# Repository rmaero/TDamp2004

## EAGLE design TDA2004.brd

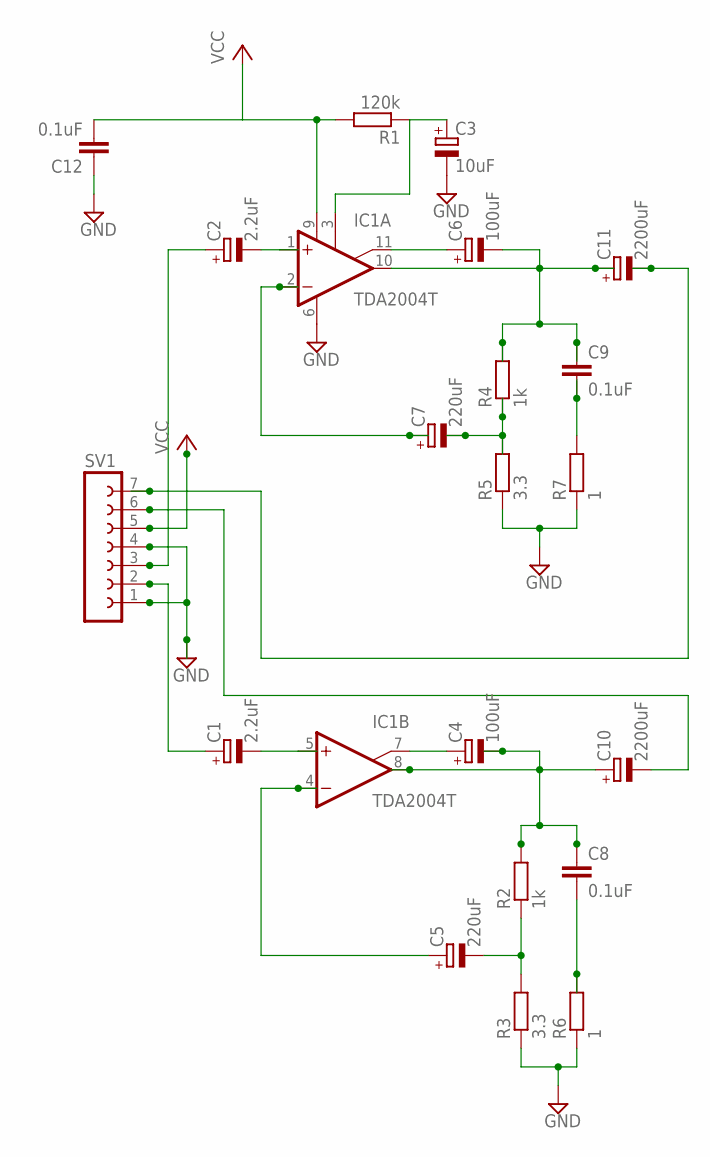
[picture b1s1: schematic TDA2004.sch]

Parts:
C1, C2: 2.2uF; B45181B
C3: 10uF; B45181B
C4, C6: 100uF; E2,5-5
C5, C7: 220uF; B45181B
C8, C9, C12: 0.1uF; C025-024X044
C10, C11: 2200uF; E5-10,5
IC1: TDA2004T; SIP11
R1: 120k; 0207/10
R2, R4: 1k; 0207/10
R3, R5: 3.3; 0207/10
R6, R7: 1; 0207/10
SV1: FE07-1; FE07

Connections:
GND: C3.-, C12.1, IC1.6 (GND), R3.1, R5.1, R6.1, R7.1, SV1.1, SV1.4
unnamed: C3.+, IC1.3 (SVRR), R1.1
unnamed: C9.2, R7.2
unnamed: C6.-, C9.1, C11.+, IC1.10 (OUT), R4.2
unnamed: C6.+, IC1.11 (BTSP)
unnamed: C2.-, IC1.1 (+IN)
unnamed: C7.+, IC1.2 (-IN)
unnamed: C10.-, SV1.6
unnamed: C4.+, IC1.7 (BTSP)
unnamed: C7.-, R4.1, R5.2
unnamed: C1.-, IC1.5 (+IN)
unnamed: C5.-, R2.1, R3.2
unnamed: C8.2, R6.2
unnamed: C11.-, SV1.7
unnamed: C5.+, IC1.4 (-IN)
unnamed: C4.-, C8.1, C10.+, IC1.8 (OUT), R2.2
unnamed: C1.+, SV1.2
unnamed: C2.+, SV1.3
VCC: C12.2, IC1.9 (V+), R1.2, SV1.5

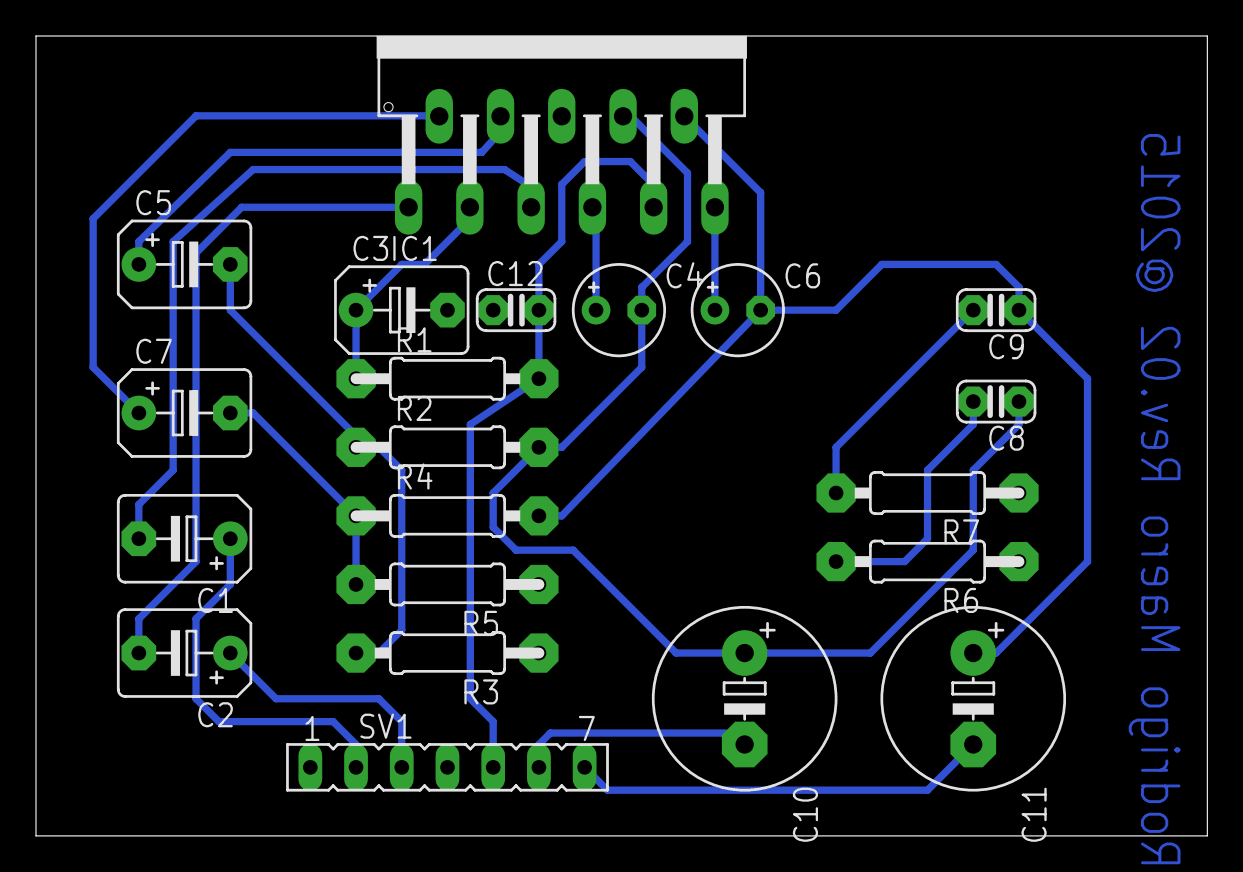
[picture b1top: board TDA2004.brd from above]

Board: 2 copper layers, 65.1 x 44.4 mm, 21 parts (0 on the bottom side), 19 nets.

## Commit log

2015-07-01 commit inicial
